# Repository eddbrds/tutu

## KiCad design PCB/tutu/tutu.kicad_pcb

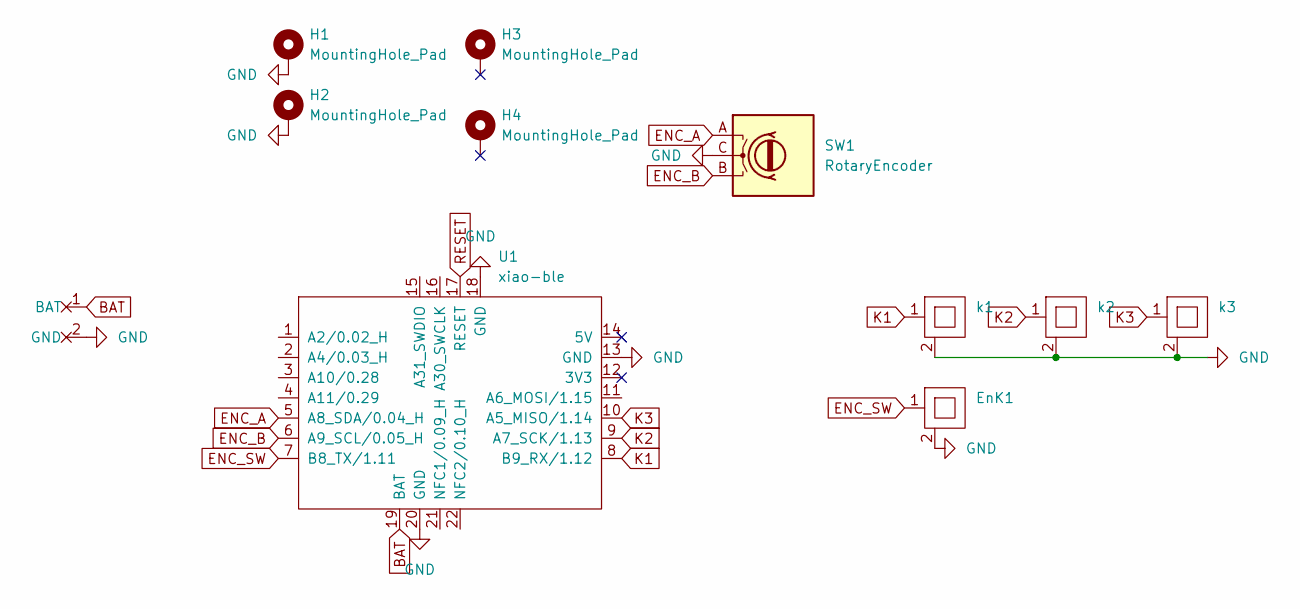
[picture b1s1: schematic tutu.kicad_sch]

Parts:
B1: Battery_THT
EnK1: Mouse Micro Switch
H1, H2: MountingHole_Pad; M2_
H3, H4: MountingHole_Pad; hole 1_mm
SW1: RotaryEncoder; Mouse encoder 3 pin
U1: xiao-ble; xiao-ble-smd
k1, k2, k3: CherryMX_1u solder

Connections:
BAT: B1.1 (BAT), U1.19 (BAT)
ENC_A: SW1.A, U1.5 (A8_SDA/0.04_H)
ENC_B: SW1.B, U1.6 (A9_SCL/0.05_H)
ENC_SW: EnK1.1, U1.7 (B8_TX/1.11)
GND: B1.2 (GND), EnK1.2, H1.1, H2.1, SW1.C, U1.13 (GND), U1.18 (GND), U1.20 (GND), k1.2, k2.2, k3.2
K1: U1.8 (B9_RX/1.12), k1.1
K2: U1.9 (A7_SCK/1.13), k2.1
K3: U1.10 (A5_MISO/1.14), k3.1
RESET: U1.17 (RESET)

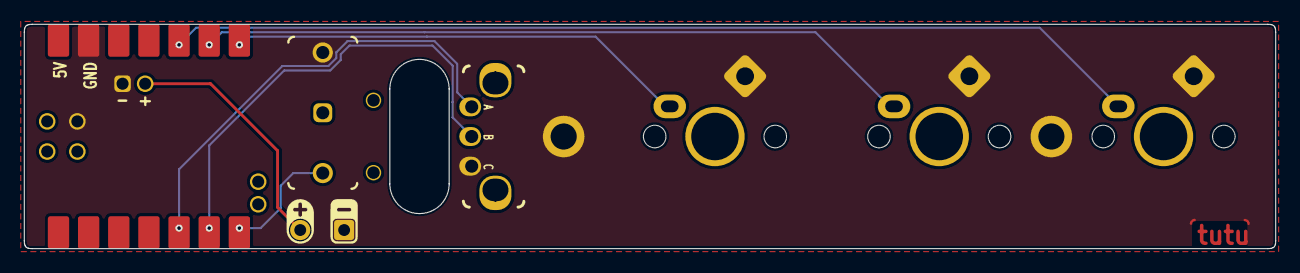
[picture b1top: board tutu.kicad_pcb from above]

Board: 2 copper layers, 105.5 x 18.9 mm, 11 parts (0 on the bottom side), 8 nets.

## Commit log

2026-01-13 Create e
